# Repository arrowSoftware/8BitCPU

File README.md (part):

# 8BitCPU
8-Bit CPU

# Table of Contents
- [References](#references)
- [TODO](#todo)
- [Instruction set](#instruction-set)
  - [Instructions](#instructions)
  - [Microcodes](#microcodes)
  - [Instruction microcode decriptions](#instruction-microcode-decriptions)
  - [Logisim Instructions Testing](#logisim-instructions-testing)
    - [NOP & HLT](#nop-hlt)
    - [LDA NUM](#lda-num)
    - [LDA [ADDR]](#lda-addr)
    - [STA [ADDR]](#sta-addr)
    - [LDB [NUM]](#ldb-num)
    - [LDB [ADDR]](#ldb-addr)
    - [STB [ADDR]](#stb-addr)
    - [ADD NUM](#add-num)
    - [ADD [ADDR]](#add-addr)
    - [SUB NUM](#sub-num)
    - [SUB [ADDR]](#sub-addr)
    - [AND NUM](#add-num)
    - [AND [ADDR]](#and-addr)
    - [OR NUM](#or-num)
    - [OR [ADDR]](#or-addr)
    - [XOR NUM](#xor-num)
    - [XOR [ADDR]](#xor-addr)
    - [NOTA](#nota)
    - [NOT [ADDR]](#not-addr)
    - [OUTA](#outa)
    - [OUTB](#outb)
    - [OUT NUM](#out-num)
    - [OUT [ADDR]](#out-addr)
    - [JMP [ADDR]](#jmp-addr)
    - [JPZ [ADDR]](#jpz-addr)
    - [JPC [ADDR]](#jpc-addr)
    - [RST](#rst)
    - [Fibinacci test](#fibinacci-test)
    - [Multiplication test](#multiplication-test)
- [CPU Design](#cpu-design)
  - [Register](#register)
    - [D-Flip-Flop](#d-flip-flop)
    - [Available registers in this project](#available-registers-in-this-project)
  - [Half Adder](#half-adder)
  - [Full Adder](#full-adder)
  - [8-Bit Adder](#8-bit-adder)
  - [D-Latch](#d-latch)
  - [4-Bit Binary Decoder](#4-bit-binary-decoder)
  - [Multiplexer](#multiplexer)
    - [1-Bit Multiplexer](#1-bit-multiplexer)
    - [8-Bit Multiplexer](#8-bit-multiplexer)
    - [8-Bit 2x1 Multiplexer](#8-bit-2x1-multiplexer)
    - [8-Bit 4x1 Multiplexer](#8-bit-4x1-multiplexer)
  - [8-Bit Clear](#8-bit-clear)
  - [8-Bit Inverter](#8-bit-inverter)
  - [8-Bit OR](#8-bit-or)
  - [8-Bit AND](#8-bit-and)
  - [8-Bit XOR](#8-bit-xor)
  - [8-Bit ALU](#8-bit-alu)
  - [4-Bit Decoder - 7 Segment](#4-bit-decoder---7-segment)
  - [8-Bit Decoder - 7 Segment](#8-bit-decoder---7-segment)
  - [8-Bit Reverser](#8-bit-reverser)
  - [SRAM](#sram)
    - [16-Byte SRAM](#16-byte-sram)
    - [256-Byte SRAM](#256-byte-sram)
  - [Program Loader](#program-loader)
  - [8-Bit Processor](#8-bit-processor)
- [Assembler](#assembler)
  - [Building](#building)
  - [Number Formats](#number-formats)
  - [Label Formats](#label-formats)
  - [Instruction Formats](#instruction-formats)
  - [Output files](#output-files)
  - [Example Output](#example-output)
  - [Warnings & Errors](#warnings--errors)
  - [Reference assembler outputs](#reference-assembler-outputs)
- [Objdump](#objdump)
- [Emulator](#emulator)

## References
* https://schweigi.github.io/assembler-simulator/
* https://schweigi.github.io/assembler-simulator/instruction-set.html
* https://users.informatik.haw-hamburg.de/~krabat/FH-Labor/gnupro/5_GNUPro_Utilities/c_Using_LD/ldLinker_scripts.html#example
* https://github.com/leonicolas/computer-8bits
* https://www.daniellowengrub.com/blog/2021/02/08/binary-counter
* https://github.com/hlorenzi/customasm
* https://cs.lmu.edu/~ray/notes/nasmtutorial/
### Backplane references
* https://github.com/daveho/easycpu
* https://hackaday.io/project/190621-zara80/log/218492-5-slot-stebus-backplane-rev-1
* https://tclarke.github.io/zara80/stebus-backplane.svg
* https://blondihacks.com/wp-content/uploads/2011/12/Backplane_Sch.jpg
* https://smallcomputercentral.files.wordpress.com/2018/09/modular-backplane-specification-v0-4-2018-09-19.pdf

## TODO

## Instruction set
The instruction set implemented in this project is CISC (Complex Instruction Set Computers) based.

### Instructions
|Instruction | OpCode | Description |
|:-----------|:-------|:------------|
|NOP         |0x00    |No operation. Fetches the next operation.|
|HLT         |0x01    |Stops the clock.|
|LDA NUM     |0x02    |Loads register A with the given value.|
|LDA [ADDR]  |0x03    |Loads register A with the value stored in the given memory address.|
|STA [ADDR]  |0x04    |Stores the register A value in the given memory address.|
|LDB NUM     |0x05    |Loads register B with the given value.|
|LDB [ADDR]  |0x06    |Loads register B with the value stored in the given memory address.|
|STB [ADDR]  |0x07    |Stores the register B value in the given memory address.|
|ADD NUM     |0x08    |Adds the given value with the value stored in register A and stores the sum result in register A. The given number will be stored in register B.|
|ADD [ADDR]  |0x09    |Adds the value stored in the given memory address with the value stored in register A. Stores the sum result in register A.|
|SUB NUM     |0x0A    |Subtracts the given value with the value stored in register A and stores the subtraction result in register A. The given number will be stored in register B.|
|SUB [ADDR]  |0x0B    |Subtracts the value stored in the given memory address with the value stored in register A. Stores the subtraction result in register A.|
|AND NUM     |0x0C    |TODO|
|ADD [ADDR]  |0x0D    |TODO|
|OR NUM      |0x0E    |TODO|
|OR [ADDR]   |0x0F    |TODO|
|XOR NUM     |0x10    |TODO|
|XOR [ADDR]  |0x11    |TODO|
|NOTA        |0x12    |TODO|
|NOT [ADDR]  |0x13    |TODO|
|OUTA        |0x14    |Sets the Output register with the register A value.|
|OUTB        |0x15    |Sets the Output register with the register B value.|
|OUT NUM     |0x16    |Sets the Output register with the given value.|
|OUT [ADDR]  |0x17    |Sets the Output register with the value stored in the given memory address.|
|JMP [ADDR]  |0x18    |Jumps to the given address.|
|JPZ [ADDR]  |0x19    |Jumps to the given address if the zero flag is 1.|
|JPC [ADDR]  |0x1A    |Jumps to the given address if the carry flag is 1.|
|UNUSED      |0x1B    |Spare expansion.|
|UNUSED      |0x1C    |Spare expansion.|
|UNUSED      |0x1D    |Spare expansion.|
|RST         |0x1E    |Reset the cpu (TODO).|

### Microcodes
* FLG = FLAG REGISTER
  * FI = Enable flag register load.
    * Loads the flags register with the value currently on the data bus.
    * Available flags:
    * | Flag | Description   |
      |------|---------------|
      | CF   | Carry Flag    |
      | ZF   | Zero Flag     |
      | NF   | Negative Flag |
      | VF   | Overflow Flag |
* CL = CLOCK
  * HL = Halt clock.
    * Stops the clock.
* AR = A REGISTER
  * AI = Enable A register load.
    * Loads the A register with the value currently on the data bus.
  * AO = Enable A regsiter output.
    * Outputs the current register value to the data bus.
* ALU = ALGORITHMIC AND LOGIC UNIT
  * EO = Enable ALU output.
    * Outputs the current ALU operation result to the data bus.
  * CI = Carry in flag.
    * Carry in flag from Flag register
  * SEL = ALU operation select code
    * 3 bit number for selecting the ALU operation.
    * | code | operation      |
      |------|----------------|
      |000   | A OR B         |
      |001   | NOT A          |
      |010   | A + NOT B + Ci |
      |011   | A + B + Ci     |
      |100   | A XOR B        |
      |101   | A AND B        |
      |110   | A - 1 + Ci     |
* BR = B REGISTER
  * BI = Enable B register load.
    * Loads the A register with the value currently on the data bus.
  * BO = Enable B regsiter output.
    * Outputs the current register value to the data bus.
* MR = MEMORY REGISTER
  * MI = Enable memory register load.
    * Loads the memory register with the value currently on the data bus.
* RAM = RANDOM ACCESS MEMORY
  * RW = Enable RAM write.
    * Writes the value currently on the data bus into the selected memory banks.
  * RR = Enable RAM read.
    * Outputs the value stored in the selected memory bank to the data bus.
* IR = INSTRUCTION REGISTER
  * II = Enable instruction register load.
    * Loads the instruction register with the value currently on the data bus.
  * IR = Reset instruction register.
    * Resets the instruction decoder counter back to 0. (Fetch next instruction set)
* PC = PROGRAM COUNTER REGISTER
  * CE = Enable counter register.
    * Enables the program counter to process the count.
  * CO = Enable counter register output.
    * Ouputs the current register value to the data bus.
  * JP = Enable counter register load.
    * Loads the program counter register with the value currently on the data bus.
* OR = OUTPUT REGISTER
  * OI = Enable output register load.
    * Loads the output register with the value currently on the data bus.

### Instruction microcode decriptions

* Control Flags is a bit mapping of each microword.
* OpCode in column 2 is the assembly opcode value.
* OpCode in second to last column is the microcode opcode value.

| Instruction | OpCode |CF |ZF |VF |NF |Step  |FI |HL |AI |AO |SEL  |EO |CI |BI |BO |MI |RW |RR |II |IR |CE |CO |JP |OI |OpCode  |Control Flags  |
|:------------|:------:|:-:|:-:|:-:|:-:|:----:|:-:|:-:|:-:|:-:|:---:|:-:|:-:|:-:|:-:|:-:|:-:|:-:|:-:|:-:|:-:|:-:|:-:|:-:|:------:|:-------------:|
|FETCH INSTR  |XXXXX   | X | X | X | X |0     | 0 | 0 | 0 | 0 | XXX | 0 | 0 | 0 | 0 | 1 | 0 | 0 | 0 | 0 | 0 | 1 | 0 | 0 | XX     | 00104         |
|             |XXXXX   | X | X | X | X |1     | 0 | 0 | 0 | 0 | XXX | 0 | 0 | 0 | 0 | 0 | 0 | 1 | 1 | 0 | 1 | 0 | 0 | 0 | XX     | 00068         |
|FIN INSTR    |XXXXX   | X | X | X | X |X     | X | X | X | 0 | XXX | 0 | 0 | 0 | 0 | 0 | 0 | 0 | 0 | 1 | 0 | 0 | 0 | 0 | XX     | 00010         |
|             |        |   |   |   |   |      |   |   |   |   |     |   |   |   |   |   |   |   |   |   |   |   |   |   |        |               |
|NOP          |00000   | X | X | X | X |2     | 0 | 0 | 0 | 0 | XXX | 0 | 0 | 0 | 0 | 0 | 0 | 0 | 0 | 1 | 0 | 0 | 0 | 0 | 00     | 00010         |
|HLT          |00001   | X | X | X | X |2     | 0 | 1 | 0 | 0 | XXX | 0 | 0 | 0 | 0 | 0 | 0 | 0 | 0 | 0 | 0 | 0 | 0 | 0 | 01     | 40000         |
|LDA NUM      |00010   | X | X | X | X |2     | 0 | 0 | 0 | 0 | XXX | 0 | 0 | 0 | 0 | 1 | 0 | 0 | 0 | 0 | 1 | 1 | 0 | 0 | 02     | 0010C         |
|             |00010   | X | X | X | X |3     | 0 | 0 | 1 | 0 | XXX | 0 | 0 | 0 | 0 | 0 | 0 | 1 | 0 | 0 | 0 | 0 | 0 | 0 | 02     | 20040         |
|LDA [ADDR]   |00011   | X | X | X | X |2     | 0 | 0 | 0 | 0 | XXX | 0 | 0 | 0 | 0 | 1 | 0 | 0 | 0 | 0 | 1 | 1 | 0 | 0 | 03     | 0010C         |
|             |00011   | X | X | X | X |3     | 0 | 0 | 0 | 0 | XXX | 0 | 0 | 0 | 0 | 1 | 0 | 1 | 0 | 0 | 0 | 0 | 0 | 0 | 03     | 00140         |
|             |00011   | X | X | X | X |4     | 0 | 0 | 1 | 0 | XXX | 0 | 0 | 0 | 0 | 0 | 0 | 1 | 0 | 0 | 0 | 0 | 0 | 0 | 03     | 20040         |
|STA [ADDR]   |00100   | X | X | X | X |2     | 0 | 0 | 0 | 0 | XXX | 0 | 0 | 0 | 0 | 1 | 0 | 0 | 0 | 0 | 1 | 1 | 0 | 0 | 04     | 0010C         |
|             |        | X | X | X | X |3     | 0 | 0 | 0 | 0 | XXX | 0 | 0 | 0 | 0 | 1 | 0 | 1 | 0 | 0 | 0 | 0 | 0 | 0 | 04     | 00140         |
|             |        | X | X | X | X |4     | 0 | 0 | 0 | 1 | XXX | 0 | 0 | 0 | 0 | 0 | 1 | 0 | 0 | 0 | 0 | 0 | 0 | 0 | 04     | 10080         |
|LDB NUM      |00101   | X | X | X | X |2     | 0 | 0 | 0 | 0 | XXX | 0 | 0 | 0 | 0 | 1 | 0 | 0 | 0 | 0 | 1 | 1 | 0 | 0 | 05     | 0010C         |
|             |        | X | X | X | X |3     | 0 | 0 | 0 | 0 | XXX | 0 | 0 | 1 | 0 | 0 | 0 | 1 | 0 | 0 | 0 | 0 | 0 | 0 | 05     | 00440         |
|LDB [ADDR]   |00110   | X | X | X | X |2     | 0 | 0 | 0 | 0 | XXX | 0 | 0 | 0 | 0 | 1 | 0 | 0 | 0 | 0 | 1 | 1 | 0 | 0 | 06     | 0010C         |
|             |        | X | X | X | X |3     | 0 | 0 | 0 | 0 | XXX | 0 | 0 | 0 | 0 | 1 | 0 | 1 | 0 | 0 | 0 | 0 | 0 | 0 | 06     | 00140         |
|             |        | X | X | X | X |4     | 0 | 0 | 0 | 0 | XXX | 0 | 0 | 1 | 0 | 0 | 0 | 1 | 0 | 0 | 0 | 0 | 0 | 0 | 06     | 00440         |
|STB [ADDR]   |00111   | X | X | X | X |2     | 0 | 0 | 0 | 0 | XXX | 0 | 0 | 0 | 0 | 1 | 0 | 0 | 0 | 0 | 1 | 1 | 0 | 0 | 07     | 0010C         |
|             |        | X | X | X | X |3     | 0 | 0 | 0 | 0 | XXX | 0 | 0 | 0 | 0 | 1 | 0 | 1 | 0 | 0 | 0 | 0 | 0 | 0 | 07     | 00140         |
|             |        | X | X | X | X |4     | 0 | 0 | 0 | 0 | XXX | 0 | 0 | 0 | 1 | 0 | 1 | 0 | 0 | 0 | 0 | 0 | 0 | 0 | 07     | 00280         |
|ADD NUM      |01000   | 0 | X | X | X |2     | 0 | 0 | 0 | 0 | 001 | 0 | 0 | 0 | 0 | 1 | 0 | 0 | 0 | 0 | 1 | 1 | 0 | 0 | 08     | 0010C         |
|             |        | 0 | X | X | X |3     | 0 | 0 | 0 | 0 | 001 | 0 | 0 | 1 | 0 | 0 | 0 | 1 | 0 | 0 | 0 | 0 | 0 | 0 | 08     | 00440         |
|             |        | 0 | X | X | X |4     | 1 | 0 | 1 | 0 | 001 | 1 | 0 | 0 | 0 | 0 | 0 | 0 | 0 | 0 | 0 | 0 | 0 | 0 | 08     | A1000         |
|ADD [ADDR]   |01001   | 0 | X | X | X |2     | 0 | 0 | 0 | 0 | 001 | 0 | 0 | 0 | 0 | 1 | 0 | 0 | 0 | 0 | 1 | 1 | 0 | 0 | 09     | 0010C         |
|             |        | 0 | X | X | X |3     | 0 | 0 | 0 | 0 | 001 | 0 | 0 | 0 | 0 | 1 | 0 | 1 | 0 | 0 | 0 | 0 | 0 | 0 | 09     | 00140         |
|             |        | 0 | X | X | X |4     | 0 | 0 | 0 | 0 | 001 | 0 | 0 | 1 | 0 | 0 | 0 | 1 | 0 | 0 | 0 | 0 | 0 | 0 | 09     | 00440         |
|             |        | 0 | X | X | X |5     | 1 | 0 | 1 | 0 | 001 | 1 | 0 | 0 | 0 | 0 | 0 | 0 | 0 | 0 | 0 | 0 | 0 | 0 | 09     | A1000         |
|SUB NUM      |01010   | 1 | X | X | X |2     | 0 | 0 | 0 | 0 | 001 | 0 | 0 | 0 | 0 | 1 | 0 | 0 | 0 | 0 | 1 | 1 | 0 | 0 | 0A     | 0010C         |
|             |        | 1 | X | X | X |3     | 0 | 0 | 0 | 0 | 001 | 0 | 1 | 1 | 0 | 0 | 0 | 1 | 0 | 0 | 0 | 0 | 0 | 0 | 0A     | 00C40         |
|             |        | 1 | X | X | X |4     | 1 | 0 | 1 | 0 | 001 | 1 | 1 | 0 | 0 | 0 | 0 | 0 | 0 | 0 | 0 | 0 | 0 | 0 | 0A     | A1800         |
|SUB [ADDR]   |01011   | 1 | X | X | X |2     | 0 | 0 | 0 | 0 | 001 | 0 | 0 | 0 | 0 | 1 | 0 | 0 | 0 | 0 | 1 | 1 | 0 | 0 | 0B     | 0010C         |
|             |        | 1 | X | X | X |3     | 0 | 0 | 0 | 0 | 001 | 0 | 0 | 0 | 0 | 1 | 0 | 1 | 0 | 0 | 0 | 0 | 0 | 0 | 0B     | 00140         |
|             |        | 1 | X | X | X |4     | 0 | 0 | 0 | 0 | 001 | 0 | 1 | 1 | 0 | 0 | 0 | 1 | 0 | 0 | 0 | 0 | 0 | 0 | 0B     | 00C40         |
|             |        | 1 | X | X | X |5     | 1 | 0 | 1 | 0 | 001 | 1 | 1 | 0 | 0 | 0 | 0 | 0 | 0 | 0 | 0 | 0 | 0 | 0 | 0B     | A1800         |
|AND NUM      |01100   | 1 | 1 | X | X |TODO  |   |   |   |   |     |   |   |   |   |   |   |   |   |   |   |   |   |   | 0C     | 00000         |
|AND [ADDR]   |01101   | 1 | 1 | X | X |TODO  |   |   |   |   |     |   |   |   |   |   |   |   |   |   |   |   |   |   | 0D     | 00000         |
|OR NUM       |01110   | 1 | 1 | X | X |TODO  |   |   |   |   |     |   |   |   |   |   |   |   |   |   |   |   |   |   | 0E     | 00000         |
|OR [ADDR]    |01111   | 1 | 1 | X | X |TODO  |   |   |   |   |     |   |   |   |   |   |   |   |   |   |   |   |   |   | 0F     | 00000         |
|XOR NUM      |10000   | 1 | 1 | X | X |TODO  |   |   |   |   |     |   |   |   |   |   |   |   |   |   |   |   |   |   | 10     | 00000         |
|XOR [ADDR]   |10001   | 1 | 1 | X | X |TODO  |   |   |   |   |     |   |   |   |   |   |   |   |   |   |   |   |   |   | 11     | 00000         |
|NOTA         |10010   | X | 1 | X | X |TODO  |   |   |   |   |     |   |   |   |   |   |   |   |   |   |   |   |   |   | 12     | 00000         |
|NOT [ADDR]   |10011   | X | 1 | X | X |TODO  |   |   |   |   |     |   |   |   |   |   |   |   |   |   |   |   |   |   | 13     | 00000         |
|OUTA         |10100   | X | X | X | X |2     | 0 | 0 | 0 | 1 | 000 | 0 | 0 | 0 | 0 | 0 | 0 | 0 | 0 | 0 | 0 | 0 | 0 | 1 | 14     | 10001         |
|OUTB         |10101   | X | X | X | X |2     | 0 | 0 | 0 | 0 | 000 | 0 | 0 | 0 | 1 | 0 | 0 | 0 | 0 | 0 | 0 | 0 | 0 | 1 | 15     | 00201         |
|OUT NUM      |10110   | X | X | X | X |2     | 0 | 0 | 0 | 0 | 000 | 0 | 0 | 0 | 0 | 1 | 0 | 0 | 0 | 0 | 1 | 1 | 0 | 0 | 16     | 0010C         |
|             |        | X | X | X | X |3     | 0 | 0 | 0 | 0 | 000 | 0 | 0 | 0 | 0 | 0 | 0 | 1 | 0 | 0 | 0 | 0 | 0 | 1 | 16     | 00041         |
|OUT [ADDR]   |10111   | X | X | X | X |2     | 0 | 0 | 0 | 0 | 000 | 0 | 0 | 0 | 0 | 1 | 0 | 0 | 0 | 0 | 1 | 1 | 0 | 0 | 17     | 0010C         |
|             |        | X | X | X | X |3     | 0 | 0 | 0 | 0 | 000 | 0 | 0 | 0 | 0 | 1 | 0 | 1 | 0 | 0 | 0 | 0 | 0 | 0 | 17     | 00140         |
|             |        | X | X | X | X |4     | 0 | 0 | 0 | 0 | 000 | 0 | 0 | 0 | 0 | 0 | 0 | 1 | 0 | 0 | 0 | 0 | 0 | 1 | 17     | 00041         |
|JMP [ADDR]   |11000   | X | X | X | X |2     | 0 | 0 | 0 | 0 | 000 | 0 | 0 | 0 | 0 | 1 | 0 | 0 | 0 | 0 | 1 | 1 | 0 | 0 | 18     | 0010C         |
|             |        | X | X | X | X |3     | 0 | 0 | 0 | 0 | 000 | 0 | 0 | 0 | 0 | 0 | 0 | 1 | 0 | 0 | 0 | 0 | 1 | 0 | 18     | 00042         |
|JPZ [ADDR]   |11001   | X | 0 | X | X |2     | 0 | 0 | 0 | 0 | 000 | 0 | 0 | 0 | 0 | 0 | 0 | 0 | 0 | 0 | 1 | 0 | 0 | 0 | 19     | 00008         |
|JPZ [ADDR]   |11001   | X | 1 | X | X |2     | 0 | 0 | 0 | 0 | 000 | 0 | 0 | 0 | 0 | 1 | 0 | 0 | 0 | 0 | 1 | 1 | 0 | 0 | 19     | 0010C         |
|             |        | X | 1 | X | X |3     | 0 | 0 | 0 | 0 | 000 | 0 | 0 | 0 | 0 | 0 | 0 | 1 | 0 | 0 | 0 | 0 | 1 | 0 | 19     | 00042         |
|JPC [ADDR]   |11001   | 0 | X | X | X |2     | 0 | 0 | 0 | 0 | 000 | 0 | 0 | 0 | 0 | 0 | 0 | 0 | 0 | 0 | 1 | 0 | 0 | 0 | 1A     | 00008         |
|JPC [ADDR]   |11010   | 1 | X | X | X |2     | 0 | 0 | 0 | 0 | 000 | 0 | 0 | 0 | 0 | 1 | 0 | 0 | 0 | 0 | 1 | 1 | 0 | 0 | 1A     | 0010C         |
|             |11011   | 1 | X | X | X |3     | 0 | 0 | 0 | 0 | 000 | 0 | 0 | 0 | 0 | 0 | 0 | 1 | 0 | 0 | 0 | 0 | 1 | 0 | 1A     | 00042         |
|UNUSED       |11100   |   |   |   |   |      |   |   |   |   |     |   |   |   |   |   |   |   |   |   |   |   |   |   | 1B     | 00000         |
|UNUSED       |11101   |   |   |   |   |      |   |   |   |   |     |   |   |   |   |   |   |   |   |   |   |   |   |   | 1C     | 00000         |
|UNUSED       |11110   |   |   |   |   |      |   |   |   |   |     |   |   |   |   |   |   |   |   |   |   |   |   |   | 1D     | 00000         |
|RST          |11111   |   |   |   |   |TODO  |   |   |   |   |     |   |   |   |   |   |   |   |   |   |   |   |   |   | 1E     | 00000         |

### Logisim Instructions Testing

#### NOP & HLT
```nasm
00:  NOP # No operation
01:  HLT # Halt the clock
```
```nasm
v2.0 raw
00
01
```

#### LDA NUM
```nasm
00:  LDA 0x55 # Load A register with value 0x55
02:  HLT # Halt the clock
```
```nasm
v2.0 raw
02 55
01
```

#### LDA [ADDR]
```nasm
# 0x04 variable

00:  LDA [variable] # Load A register with value at address [variable]
02:  HLT # Halt the clock
```
```nasm
v2.0 raw
03 04
01 00
aa 00
```

#### STA [ADDR]
```nasm
# 0x05 variablePtr

00: LDA 0xAA # Load A register with value 0xAA
02: STA [variablePtr] # Store value in A register at memory address [variablePtr]
04: HLT # Halt the clock
```
```nasm
v2.0 raw
02 55
04 05
01
```

#### LDB [NUM]
```nasm
00:  LDB 0x55 # Load B register with value 0x55
02:  HLT # Halt the clock
```
```nasm
v2.0 raw
05 55
01
```

#### LDB [ADDR]
```nasm
# 0x04 variable

00:  LDB [variable] # Load B register with value at address [variable]
02:  HLT # Halt the clock
```
```nasm
v2.0 raw
06 04
01 00
aa 00
```

#### STB [ADDR]
```nasm
# 0x05 variablePtr

00: LDB 0xAA # Load B register with value 0xAA
02: STB [variablePtr] # Store value in B register at memory address [variablePtr]
04: HLT # Halt the clock
```
```nasm
v2.0 raw
05 55
07 05
01
```

#### ADD NUM
```nasm
00: LDA 0x02 # Load A register with value 0x02
02: ADD 0x04 # Add 0x04 to the value in A register and store output in A register
04: OUTA # Load output register with the value in the A register
05: HLT # halt the clock
```
```nasm
v2.0 raw
02 02
08 04
14
01
```

#### ADD [ADDR]
```nasm
# 0x07 variablePtr

00: LDA 0x5
02: ADD [variablePtr] # Add the value in memory address [variablePtr] to the value in the A register and store the output in the A register
04: OUTA # Load output register with the value in the A register
05: HLT # halt the clock
```
```nasm
v2.0 raw
02 05
09 07
14
01
00
05
```

#### SUB NUM
```nasm
00: LDA 0x08
02: SUB 0x02
04: OUTA
05: HLT
```
``` nasm
v2.0 raw
02 08
0A 02
14
01
```

#### SUB [ADDR]
```nasm
# 0x07 variablePtr

00: LDA 0x08
02: SUB [variablePtr] # Subtract the value in memory address [variablePtr] from the value in the A register and store the output in the A register
04: OUTA
05: HLT
```
``` nasm
v2.0 raw
02 08
0B 07
14
01
00
02
```

#### AND NUM
```nasm
TODO
```
```nasm
v2.0 raw
```

#### AND [ADDR]
```nasm
TODO
```
```nasm
v2.0 raw
```
![AND [ADDR] test](/Images/Test_AND_ADDR.gif)

#### OR NUM
```nasm
TODO
```
```nasm
v2.0 raw
```

#### OR [ADDR]
```nasm
TODO
```
```nasm
v2.0 raw
```
![OR [ADDR] test](/Images/Test_OR_ADDR.gif)

#### XOR NUM
```nasm
TODO
```
```nasm
v2.0 raw
```

#### XOR [ADDR]
```nasm
TODO
```
```nasm
v2.0 raw
```
![XOR [ADDR] test](/Images/Test_XOR_ADDR.gif)

#### NOTA
```nasm
TODO
```
```nasm
v2.0 raw
```

#### NOT [ADDR]
```nasm
TODO
```
```nasm
v2.0 raw
```
![NOT [ADDR] test](/Images/Test_NOT_ADDR.gif)

#### OUTA
```nasm
00: LDA 0x55 # Load A register with value 0x55
02: OUTA
03: HLT
```
```nasm
v2.0 raw
02 55
14
01
```

#### OUTB
```nasm
00: LDB 0x55 # Load B register with value 0x55
02: OUTB
03: HLT
```
```nasm
v2.0 raw
05 55
15
01
```

#### OUT NUM
```nasm
00: OUT 0xAA
02: HLT
```
```nasm
v2.0 raw
16 aa
01
```

#### OUT [ADDR]
```nasm
# 0x04 variablePtr

00: OUT [variablePtr]
02: HLT

```
```nasm
v2.0 raw
17 04
01
00
55
```

#### JMP [ADDR]
```nasm
JMP 0x20

# address 0x20
LDA 0x55
OUTA
HLT
```
```nasm
v2.0 raw
00: 18 10
...
10: 02 55
12: 14
13: 01
```

#### JPZ [ADDR]
ZF = 1
```nasm
00: LDA 0x04
02: SUB 0x04
04: JPZ 0x10
06: OUT 0xFF
07: HLT
...
10: OUT 0x55
12: HLT
```
```nasm
v2.0 raw
02 04
0a 04
19 10
16 ff
01
00 00
00 00
00 00
00
16 55
01
```

ZF = 0
```nasm
00: LDA 0x04
02: ADD 0x04
04: JPZ 0x10
06: OUT 0xFF
07: HLT
...
10: OUT 0x55
12: HLT
```
```nasm
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
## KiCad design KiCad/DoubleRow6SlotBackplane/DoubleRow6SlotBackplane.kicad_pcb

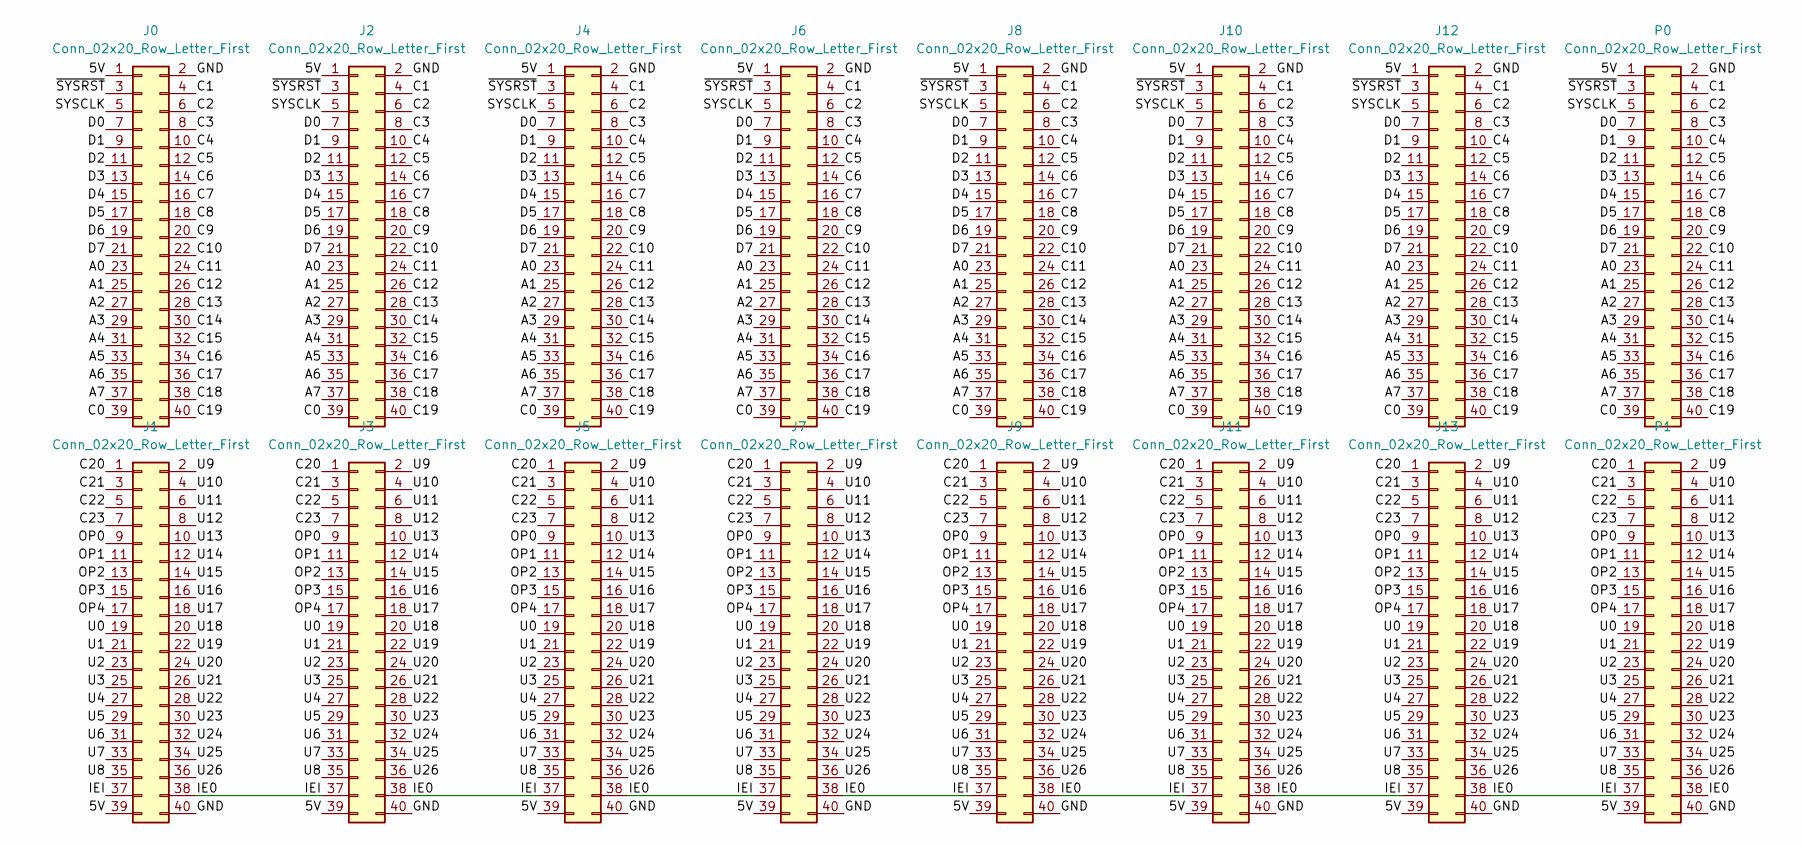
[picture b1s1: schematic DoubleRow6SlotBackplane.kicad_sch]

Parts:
J0, J1: Conn_02x20_Row_Letter_First; PinSocket_2x20_P2.54mm_Horizontal
J2, J3, J4, J5, J6, J7, J8, J9, J10, J11, J12, J13: Conn_02x20_Row_Letter_First; PinSocket_2x20_P2.54mm_Vertical
P0, P1: Conn_02x20_Row_Letter_First; PinHeader_2x20_P2.54mm_Horizontal

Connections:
/5V: J0.1, J1.39, J2.1, J3.39, J4.1, J5.39, J6.1, J7.39, J8.1, J9.39, J10.1, J11.39, J12.1, J13.39, P0.1, P1.39
/A0: J0.23, J2.23, J4.23, J6.23, J8.23, J10.23, J12.23, P0.23
/A1: J0.25, J2.25, J4.25, J6.25, J8.25, J10.25, J12.25, P0.25
/A2: J0.27, J2.27, J4.27, J6.27, J8.27, J10.27, J12.27, P0.27
/A3: J0.29, J2.29, J4.29, J6.29, J8.29, J10.29, J12.29, P0.29
/A4: J0.31, J2.31, J4.31, J6.31, J8.31, J10.31, J12.31, P0.31
/A5: J0.33, J2.33, J4.33, J6.33, J8.33, J10.33, J12.33, P0.33
/A6: J0.35, J2.35, J4.35, J6.35, J8.35, J10.35, J12.35, P0.35
/A7: J0.37, J2.37, J4.37, J6.37, J8.37, J10.37, J12.37, P0.37
/C0: J0.39, J2.39, J4.39, J6.39, J8.39, J10.39, J12.39, P0.39
/C1: J0.4, J2.4, J4.4, J6.4, J8.4, J10.4, J12.4, P0.4
/C2: J0.6, J2.6, J4.6, J6.6, J8.6, J10.6, J12.6, P0.6
/C3: J0.8, J2.8, J4.8, J6.8, J8.8, J10.8, J12.8, P0.8
/C4: J0.10, J2.10, J4.10, J6.10, J8.10, J10.10, J12.10, P0.10
/C5: J0.12, J2.12, J4.12, J6.12, J8.12, J10.12, J12.12, P0.12
/C6: J0.14, J2.14, J4.14, J6.14, J8.14, J10.14, J12.14, P0.14
/C7: J0.16, J2.16, J4.16, J6.16, J8.16, J10.16, J12.16, P0.16
/C8: J0.18, J2.18, J4.18, J6.18, J8.18, J10.18, J12.18, P0.18
/C9: J0.20, J2.20, J4.20, J6.20, J8.20, J10.20, J12.20, P0.20
/C10: J0.22, J2.22, J4.22, J6.22, J8.22, J10.22, J12.22, P0.22
/C11: J0.24, J2.24, J4.24, J6.24, J8.24, J10.24, J12.24, P0.24
/C12: J0.26, J2.26, J4.26, J6.26, J8.26, J10.26, J12.26, P0.26
/C13: J0.28, J2.28, J4.28, J6.28, J8.28, J10.28, J12.28, P0.28
/C14: J0.30, J2.30, J4.30, J6.30, J8.30, J10.30, J12.30, P0.30
/C15: J0.32, J2.32, J4.32, J6.32, J8.32, J10.32, J12.32, P0.32
/C16: J0.34, J2.34, J4.34, J6.34, J8.34, J10.34, J12.34, P0.34
/C17: J0.36, J2.36, J4.36, J6.36, J8.36, J10.36, J12.36, P0.36
/C18: J0.38, J2.38, J4.38, J6.38, J8.38, J10.38, J12.38, P0.38
/C19: J0.40, J2.40, J4.40, J6.40, J8.40, J10.40, J12.40, P0.40
/C20: J1.1, J3.1, J5.1, J7.1, J9.1, J11.1, J13.1, P1.1
/C21: J1.3, J3.3, J5.3, J7.3, J9.3, J11.3, J13.3, P1.3
/C22: J1.5, J3.5, J5.5, J7.5, J9.5, J11.5, J13.5, P1.5
/C23: J1.7, J3.7, J5.7, J7.7, J9.7, J11.7, J13.7, P1.7
/D0: J0.7, J2.7, J4.7, J6.7, J8.7, J10.7, J12.7, P0.7
/D1: J0.9, J2.9, J4.9, J6.9, J8.9, J10.9, J12.9, P0.9
/D2: J0.11, J2.11, J4.11, J6.11, J8.11, J10.11, J12.11, P0.11
/D3: J0.13, J2.13, J4.13, J6.13, J8.13, J10.13, J12.13, P0.13
/D4: J0.15, J2.15, J4.15, J6.15, J8.15, J10.15, J12.15, P0.15
/D5: J0.17, J2.17, J4.17, J6.17, J8.17, J10.17, J12.17, P0.17
/D6: J0.19, J2.19, J4.19, J6.19, J8.19, J10.19, J12.19, P0.19
/D7: J0.21, J2.21, J4.21, J6.21, J8.21, J10.21, J12.21, P0.21
/GND: J0.2, J1.40, J2.2, J3.40, J4.2, J5.40, J6.2, J7.40, J8.2, J9.40, J10.2, J11.40, J12.2, J13.40, P0.2, P1.40
/IE0: J1.37, J1.38, J3.37, J3.38, J5.37, J5.38, J7.37, J7.38, J9.37, J9.38, J11.37, J11.38, J13.37, J13.38, P1.37, P1.38
/OP0: J1.9, J3.9, J5.9, J7.9, J9.9, J11.9, J13.9, P1.9
/OP1: J1.11, J3.11, J5.11, J7.11, J9.11, J11.11, J13.11, P1.11
/OP2: J1.13, J3.13, J5.13, J7.13, J9.13, J11.13, J13.13, P1.13
/OP3: J1.15, J3.15, J5.15, J7.15, J9.15, J11.15, J13.15, P1.15
/OP4: J1.17, J3.17, J5.17, J7.17, J9.17, J11.17, J13.17, P1.17
/SYSCLK: J0.5, J2.5, J4.5, J6.5, J8.5, J10.5, J12.5, P0.5
/U0: J1.19, J3.19, J5.19, J7.19, J9.19, J11.19, J13.19, P1.19
/U1: J1.21, J3.21, J5.21, J7.21, J9.21, J11.21, J13.21, P1.21
/U2: J1.23, J3.23, J5.23, J7.23, J9.23, J11.23, J13.23, P1.23
/U3: J1.25, J3.25, J5.25, J7.25, J9.25, J11.25, J13.25, P1.25
/U4: J1.27, J3.27, J5.27, J7.27, J9.27, J11.27, J13.27, P1.27
/U5: J1.29, J3.29, J5.29, J7.29, J9.29, J11.29, J13.29, P1.29
/U6: J1.31, J3.31, J5.31, J7.31, J9.31, J11.31, J13.31, P1.31
/U7: J1.33, J3.33, J5.33, J7.33, J9.33, J11.33, J13.33, P1.33
/U8: J1.35, J3.35, J5.35, J7.35, J9.35, J11.35, J13.35, P1.35
/U9: J1.2, J3.2, J5.2, J7.2, J9.2, J11.2, J13.2, P1.2
/U10: J1.4, J3.4, J5.4, J7.4, J9.4, J11.4, J13.4, P1.4
/U11: J1.6, J3.6, J5.6, J7.6, J9.6, J11.6, J13.6, P1.6
/U12: J1.8, J3.8, J5.8, J7.8, J9.8, J11.8, J13.8, P1.8
/U13: J1.10, J3.10, J5.10, J7.10, J9.10, J11.10, J13.10, P1.10
/U14: J1.12, J3.12, J5.12, J7.12, J9.12, J11.12, J13.12, P1.12
/U15: J1.14, J3.14, J5.14, J7.14, J9.14, J11.14, J13.14, P1.14
/U16: J1.16, J3.16, J5.16, J7.16, J9.16, J11.16, J13.16, P1.16
/U17: J1.18, J3.18, J5.18, J7.18, J9.18, J11.18, J13.18, P1.18
/U18: J1.20, J3.20, J5.20, J7.20, J9.20, J11.20, J13.20, P1.20
/U19: J1.22, J3.22, J5.22, J7.22, J9.22, J11.22, J13.22, P1.22
/U20: J1.24, J3.24, J5.24, J7.24, J9.24, J11.24, J13.24, P1.24
/U21: J1.26, J3.26, J5.26, J7.26, J9.26, J11.26, J13.26, P1.26
/U22: J1.28, J3.28, J5.28, J7.28, J9.28, J11.28, J13.28, P1.28
/U23: J1.30, J3.30, J5.30, J7.30, J9.30, J11.30, J13.30, P1.30
/U24: J1.32, J3.32, J5.32, J7.32, J9.32, J11.32, J13.32, P1.32
/U25: J1.34, J3.34, J5.34, J7.34, J9.34, J11.34, J13.34, P1.34
/U26: J1.36, J3.36, J5.36, J7.36, J9.36, J11.36, J13.36, P1.36
/~SYSRST: J0.3, J2.3, J4.3, J6.3, J8.3, J10.3, J12.3, P0.3

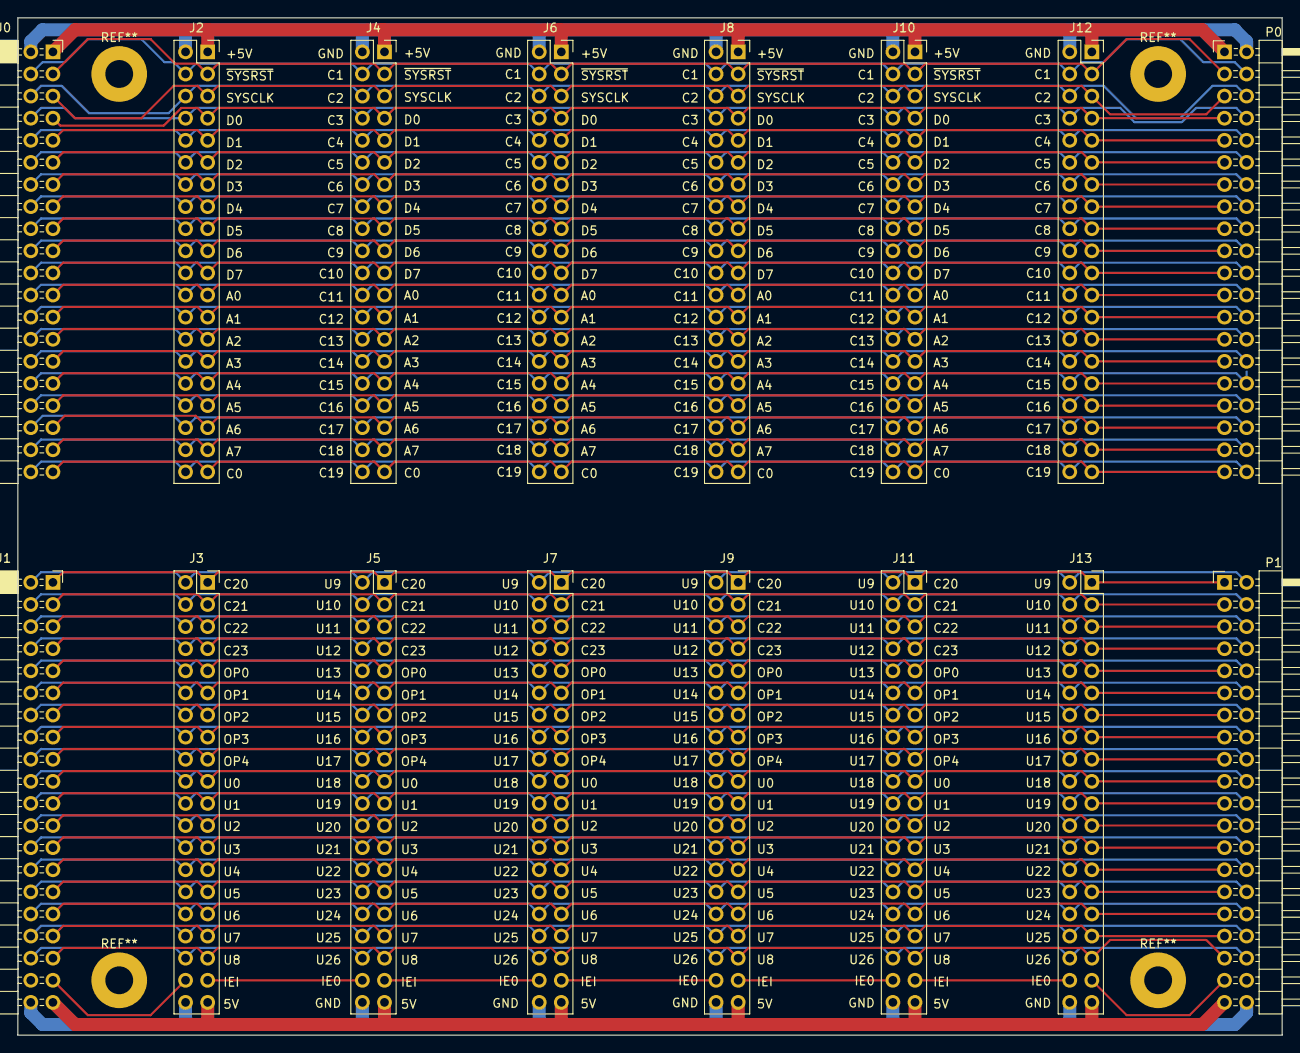
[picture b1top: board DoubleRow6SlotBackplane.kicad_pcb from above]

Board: 2 copper layers, 145.3 x 116.9 mm, 16 parts (0 on the bottom side), 77 nets.

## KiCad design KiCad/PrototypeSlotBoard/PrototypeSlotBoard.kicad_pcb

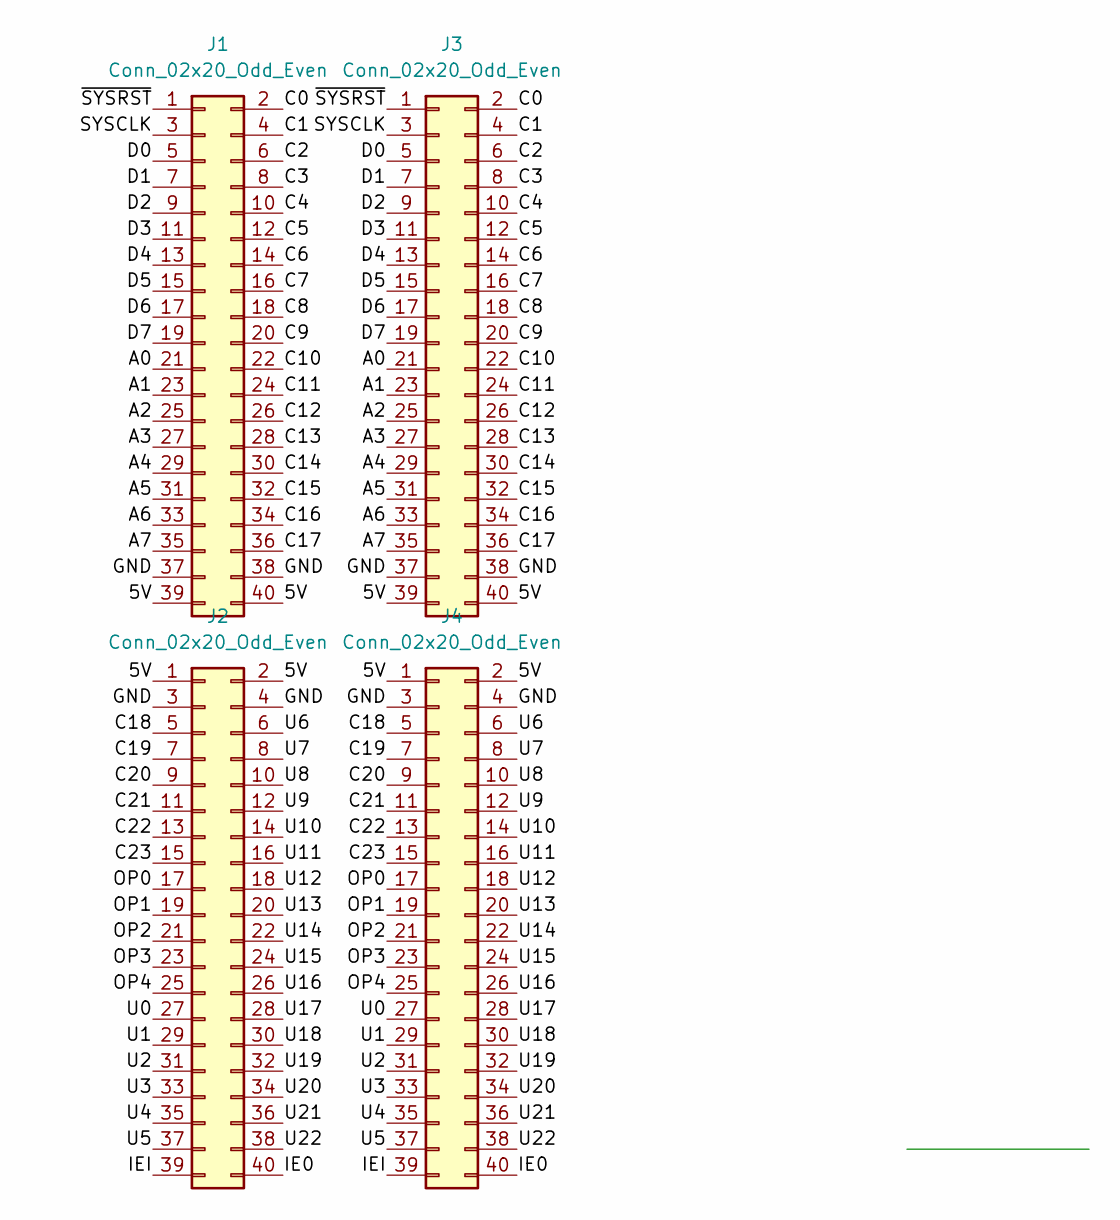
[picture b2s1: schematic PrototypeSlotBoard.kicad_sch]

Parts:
J1, J2: Conn_02x20_Odd_Even; PinHeader_2x20_P2.54mm_Horizontal
J3, J4: Conn_02x20_Odd_Even; PinHeader_2x20_P2.54mm_Vertical

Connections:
/5V: J1.39, J1.40, J2.1, J2.2, J3.39, J3.40, J4.1, J4.2
/A0: J1.21, J3.21
/A1: J1.23, J3.23
/A2: J1.25, J3.25
/A3: J1.27, J3.27
/A4: J1.29, J3.29
/A5: J1.31, J3.31
/A6: J1.33, J3.33
/A7: J1.35, J3.35
/C0: J1.2, J3.2
/C1: J1.4, J3.4
/C2: J1.6, J3.6
/C3: J1.8, J3.8
/C4: J1.10, J3.10
/C5: J1.12, J3.12
/C6: J1.14, J3.14
/C7: J1.16, J3.16
/C8: J1.18, J3.18
/C9: J1.20, J3.20
/C10: J1.22, J3.22
/C11: J1.24, J3.24
/C12: J1.26, J3.26
/C13: J1.28, J3.28
/C14: J1.30, J3.30
/C15: J1.32, J3.32
/C16: J1.34, J3.34
/C17: J1.36, J3.36
/C18: J2.5, J4.5
/C19: J2.7, J4.7
/C20: J2.9, J4.9
/C21: J2.11, J4.11
/C22: J2.13, J4.13
/C23: J2.15, J4.15
/D0: J1.5, J3.5
/D1: J1.7, J3.7
/D2: J1.9, J3.9
/D3: J1.11, J3.11
/D4: J1.13, J3.13
/D5: J1.15, J3.15
/D6: J1.17, J3.17
/D7: J1.19, J3.19
/GND: J1.37, J1.38, J2.3, J2.4, J3.37, J3.38, J4.3, J4.4
/IE0: J2.40, J4.40
/IEI: J2.39, J4.39
/OP0: J2.17, J4.17
/OP1: J2.19, J4.19
/OP2: J2.21, J4.21
/OP3: J2.23, J4.23
/OP4: J2.25, J4.25
/SYSCLK: J1.3, J3.3
/U0: J2.27, J4.27
/U1: J2.29, J4.29
/U2: J2.31, J4.31
/U3: J2.33, J4.33
/U4: J2.35, J4.35
/U5: J2.37, J4.37
/U6: J2.6, J4.6
/U7: J2.8, J4.8
/U8: J2.10, J4.10
/U9: J2.12, J4.12
/U10: J2.14, J4.14
/U11: J2.16, J4.16
/U12: J2.18, J4.18
/U13: J2.20, J4.20
/U14: J2.22, J4.22
/U15: J2.24, J4.24
/U16: J2.26, J4.26
/U17: J2.28, J4.28
/U18: J2.30, J4.30
/U19: J2.32, J4.32
/U20: J2.34, J4.34
/U21: J2.36, J4.36
/U22: J2.38, J4.38
/~SYSRST: J1.1, J3.1

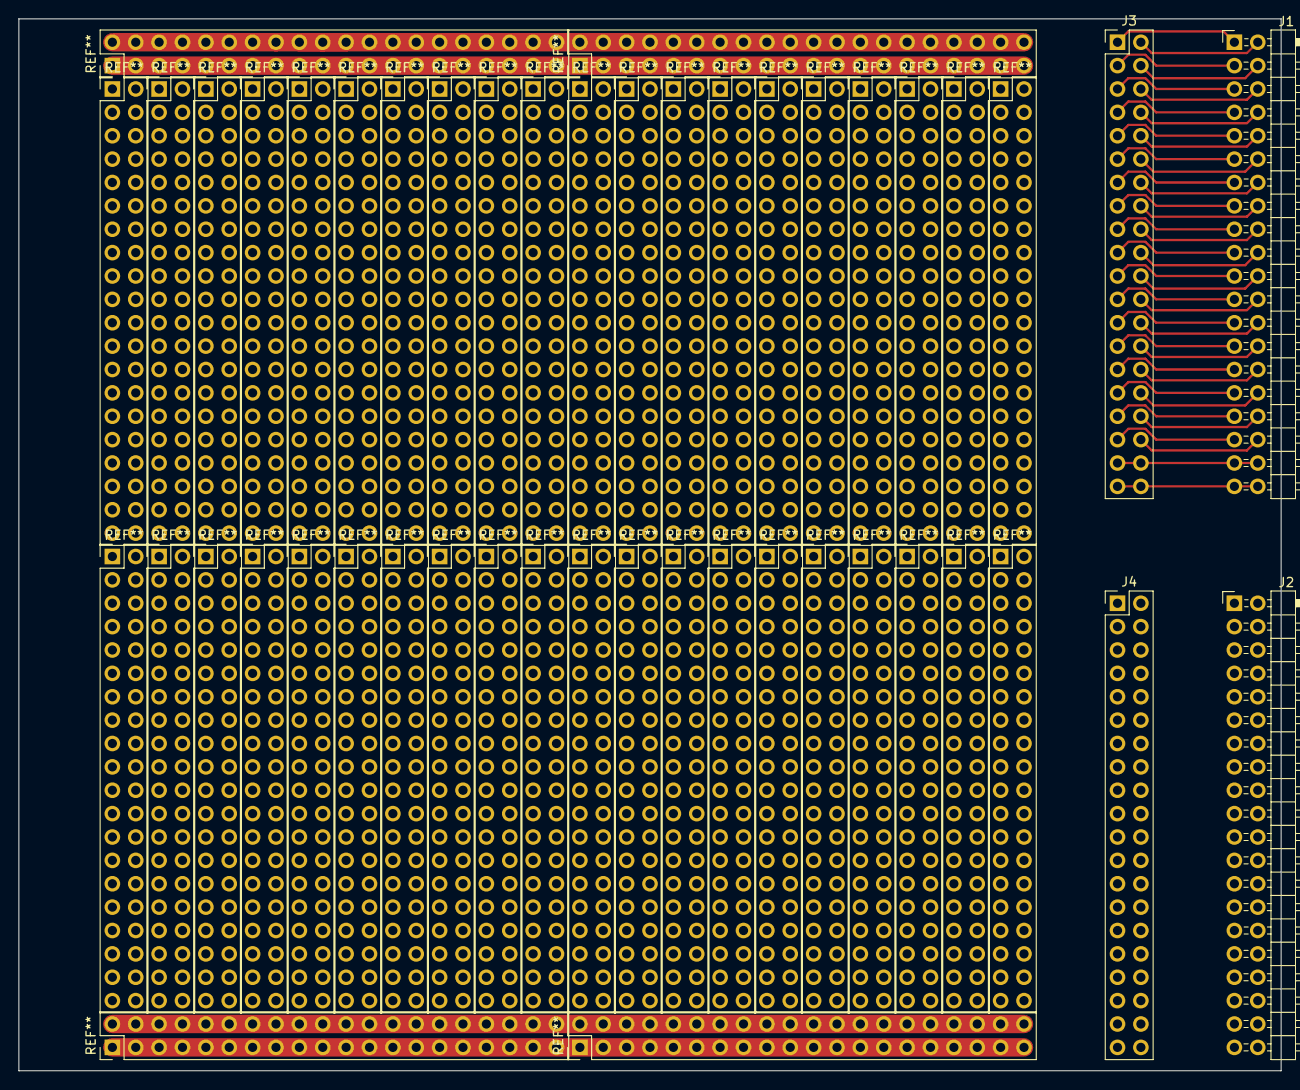
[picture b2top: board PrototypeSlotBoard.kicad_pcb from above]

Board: 2 copper layers, 137.2 x 114.3 mm, 4 parts (0 on the bottom side), 74 nets.

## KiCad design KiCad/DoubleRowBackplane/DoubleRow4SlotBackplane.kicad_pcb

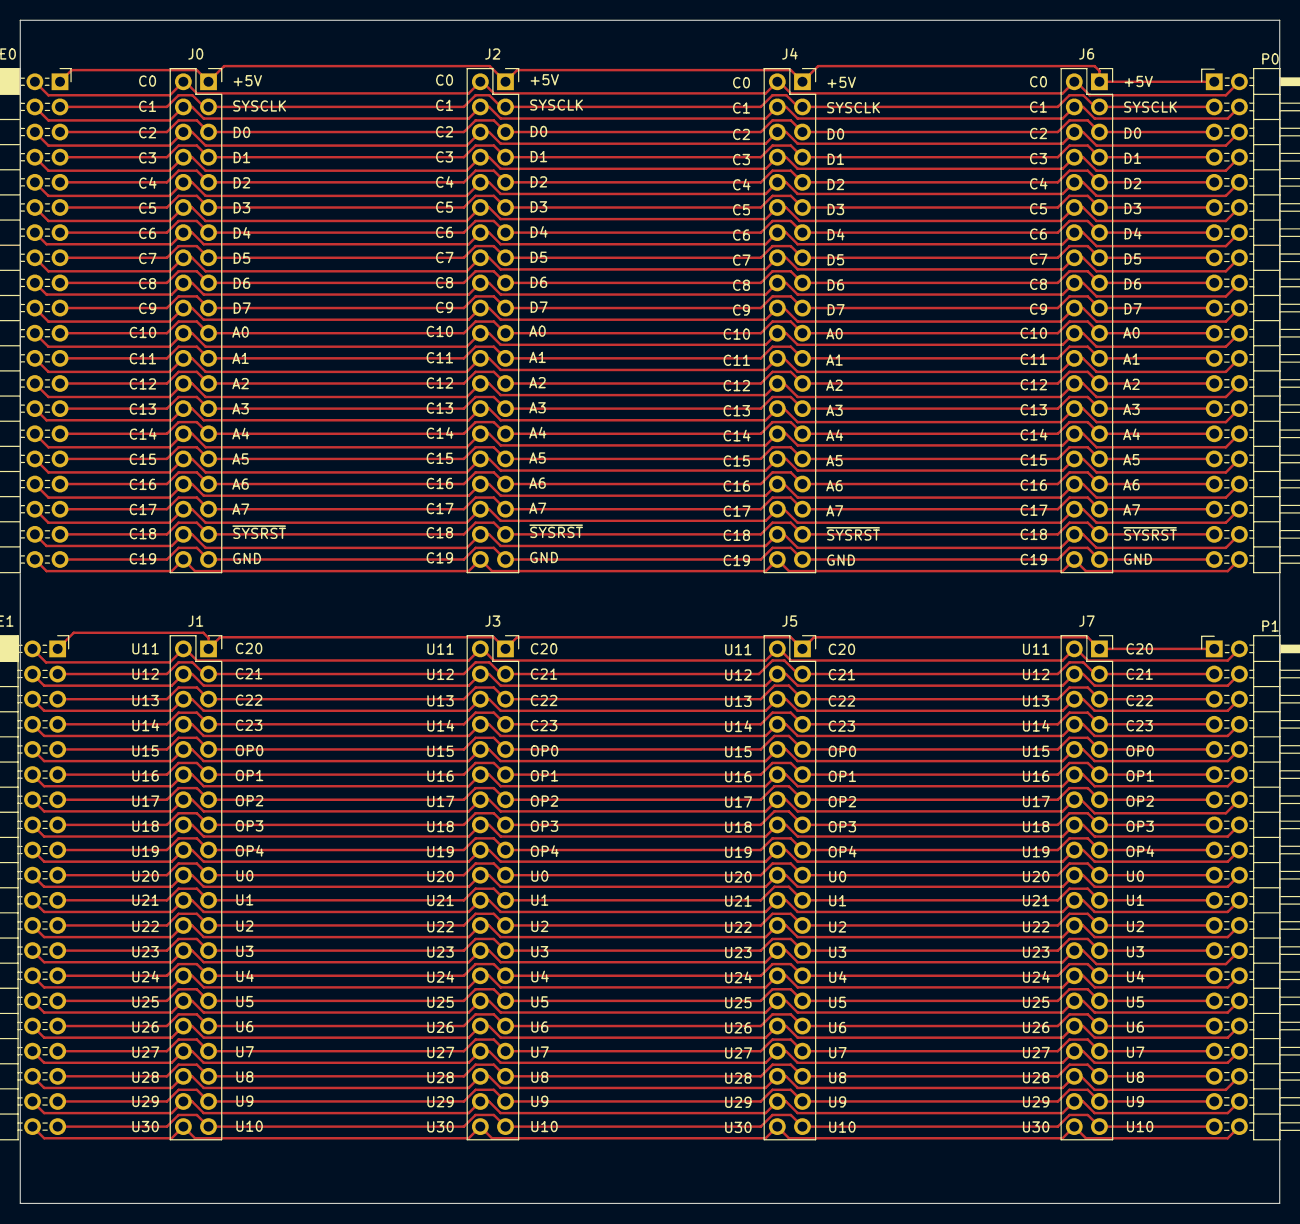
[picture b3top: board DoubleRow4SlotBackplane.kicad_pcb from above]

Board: 2 copper layers, 127.2 x 119.5 mm, 12 parts (0 on the bottom side), 80 nets.

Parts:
J0, J1, J2, J3, J4, J5, J6, J7: Conn_02x20_Row_Letter_First; PinSocket_2x20_P2.54mm_Vertical
JE0, JE1: Conn_02x20_Row_Letter_First; PinSocket_2x20_P2.54mm_Horizontal
P0, P1: Conn_02x20_Row_Letter_First; PinHeader_2x20_P2.54mm_Horizontal

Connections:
/+5V: J0.1, J2.1, J4.1, J6.1, JE0.1, P0.1
/A0: J0.21, J2.21, J4.21, J6.21, JE0.21, P0.21
/A1: J0.23, J2.23, J4.23, J6.23, JE0.23, P0.23
/A2: J0.25, J2.25, J4.25, J6.25, JE0.25, P0.25
/A3: J0.27, J2.27, J4.27, J6.27, JE0.27, P0.27
/A4: J0.29, J2.29, J4.29, J6.29, JE0.29, P0.29
/A5: J0.31, J2.31, J4.31, J6.31, JE0.31, P0.31
/A6: J0.33, J2.33, J4.33, J6.33, JE0.33, P0.33
/A7: J0.35, J2.35, J4.35, J6.35, JE0.35, P0.35
/C0: J0.2, J2.2, J4.2, J6.2, JE0.2, P0.2
/C1: J0.4, J2.4, J4.4, J6.4, JE0.4, P0.4
/C2: J0.6, J2.6, J4.6, J6.6, JE0.6, P0.6
/C3: J0.8, J2.8, J4.8, J6.8, JE0.8, P0.8
/C4: J0.10, J2.10, J4.10, J6.10, JE0.10, P0.10
/C5: J0.12, J2.12, J4.12, J6.12, JE0.12, P0.12
/C6: J0.14, J2.14, J4.14, J6.14, JE0.14, P0.14
/C7: J0.16, J2.16, J4.16, J6.16, JE0.16, P0.16
/C8: J0.18, J2.18, J4.18, J6.18, JE0.18, P0.18
/C9: J0.20, J2.20, J4.20, J6.20, JE0.20, P0.20
/C10: J0.22, J2.22, J4.22, J6.22, JE0.22, P0.22
/C11: J0.24, J2.24, J4.24, J6.24, JE0.24, P0.24
/C12: J0.26, J2.26, J4.26, J6.26, JE0.26, P0.26
/C13: J0.28, J2.28, J4.28, J6.28, JE0.28, P0.28
/C14: J0.30, J2.30, J4.30, J6.30, JE0.30, P0.30
/C15: J0.32, J2.32, J4.32, J6.32, JE0.32, P0.32
/C16: J0.34, J2.34, J4.34, J6.34, JE0.34, P0.34
/C17: J0.36, J2.36, J4.36, J6.36, JE0.36, P0.36
/C18: J0.38, J2.38, J4.38, J6.38, JE0.38, P0.38
/C19: J0.40, J2.40, J4.40, J6.40, JE0.40, P0.40
/C20: J1.1, J3.1, J5.1, J7.1, JE1.1, P1.1
/C21: J1.3, J3.3, J5.3, J7.3, JE1.3, P1.3
/C22: J1.5, J3.5, J5.5, J7.5, JE1.5, P1.5
/C23: J1.7, J3.7, J5.7, J7.7, JE1.7, P1.7
/D0: J0.5, J2.5, J4.5, J6.5, JE0.5, P0.5
/D1: J0.7, J2.7, J4.7, J6.7, JE0.7, P0.7
/D2: J0.9, J2.9, J4.9, J6.9, JE0.9, P0.9
/D3: J0.11, J2.11, J4.11, J6.11, JE0.11, P0.11
/D4: J0.13, J2.13, J4.13, J6.13, JE0.13, P0.13
/D5: J0.15, J2.15, J4.15, J6.15, JE0.15, P0.15
/D6: J0.17, J2.17, J4.17, J6.17, JE0.17, P0.17
/D7: J0.19, J2.19, J4.19, J6.19, JE0.19, P0.19
/GND: J0.39, J2.39, J4.39, J6.39, JE0.39, P0.39
/OP0: J1.9, J3.9, J5.9, J7.9, JE1.9, P1.9
/OP1: J1.11, J3.11, J5.11, J7.11, JE1.11, P1.11
/OP2: J1.13, J3.13, J5.13, J7.13, JE1.13, P1.13
/OP3: J1.15, J3.15, J5.15, J7.15, JE1.15, P1.15
/OP4: J1.17, J3.17, J5.17, J7.17, JE1.17, P1.17
/SYSCLK: J0.3, J2.3, J4.3, J6.3, JE0.3, P0.3
/U0: J1.19, J3.19, J5.19, J7.19, JE1.19, P1.19
/U1: J1.21, J3.21, J5.21, J7.21, JE1.21, P1.21
/U2: J1.23, J3.23, J5.23, J7.23, JE1.23, P1.23
/U3: J1.25, J3.25, J5.25, J7.25, JE1.25, P1.25
/U4: J1.27, J3.27, J5.27, J7.27, JE1.27, P1.27
/U5: J1.29, J3.29, J5.29, J7.29, JE1.29, P1.29
/U6: J1.31, J3.31, J5.31, J7.31, JE1.31, P1.31
/U7: J1.33, J3.33, J5.33, J7.33, JE1.33, P1.33
/U8: J1.35, J3.35, J5.35, J7.35, JE1.35, P1.35
/U9: J1.37, J3.37, J5.37, J7.37, JE1.37, P1.37
/U10: J1.39, J3.39, J5.39, J7.39, JE1.39, P1.39
/U11: J1.2, J3.2, J5.2, J7.2, JE1.2, P1.2
/U12: J1.4, J3.4, J5.4, J7.4, JE1.4, P1.4
/U13: J1.6, J3.6, J5.6, J7.6, JE1.6, P1.6
/U14: J1.8, J3.8, J5.8, J7.8, JE1.8, P1.8
/U15: J1.10, J3.10, J5.10, J7.10, JE1.10, P1.10
/U16: J1.12, J3.12, J5.12, J7.12, JE1.12, P1.12
/U17: J1.14, J3.14, J5.14, J7.14, JE1.14, P1.14
/U18: J1.16, J3.16, J5.16, J7.16, JE1.16, P1.16
/U19: J1.18, J3.18, J5.18, J7.18, JE1.18, P1.18
/U20: J1.20, J3.20, J5.20, J7.20, JE1.20, P1.20
/U21: J1.22, J3.22, J5.22, J7.22, JE1.22, P1.22
/U22: J1.24, J3.24, J5.24, J7.24, JE1.24, P1.24
/U23: J1.26, J3.26, J5.26, J7.26, JE1.26, P1.26
/U24: J1.28, J3.28, J5.28, J7.28, JE1.28, P1.28
/U25: J1.30, J3.30, J5.30, J7.30, JE1.30, P1.30
/U26: J1.32, J3.32, J5.32, J7.32, JE1.32, P1.32
/U27: J1.34, J3.34, J5.34, J7.34, JE1.34, P1.34
/U28: J1.36, J3.36, J5.36, J7.36, JE1.36, P1.36
/U29: J1.38, J3.38, J5.38, J7.38, JE1.38, P1.38
/U30: J1.40, J3.40, J5.40, J7.40, JE1.40, P1.40
/~SYSRST: J0.37, J2.37, J4.37, J6.37, JE0.37, P0.37
